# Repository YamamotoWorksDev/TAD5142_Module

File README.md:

# TAD5142 Module

This module board is a headphone output module featuring TI’s stereo audio DAC TAD5142. It supports sample rates up to 192 kHz and can add a headphone output to your microcontroller board or other hardware via an I2S connection.

## How to buy
- Tindie(International)  
- [BASE(Japan)](https://miyworks.base.shop/items/141803009)

## Specifications
- Power: 5V input, onboard 3.3V regulator (AP7361)
- DAC IC: [TAD5142](https://www.ti.com/product/TAD5142)
  - Channels: stereo output
  - Sample Rate: 192kHz(max.)
  - I2S Slave
- Audio Jack: [Green Thonkiconn Stereo 3.5mm Jack Socket](https://www.thonk.co.uk/shop/thonkiconn/)
- Power IC: [AP7361EA-33E-13](https://www.diodes.com/assets/Datasheets/AP7361EA.pdf)

## Application Example
- [JUMBLEQ](https://github.com/yamamo2shun1/JUMBLEQ)

## Size

## Photos

## License
The hardware design files in this repository are licensed under the
**CERN Open Hardware Licence Version 2 - Permissive (CERN-OHL-P-2.0)**.

Unless otherwise stated, the following are treated as hardware design files covered by CERN-OHL-P-2.0:

- KiCad schematic files
- PCB layout files

A copy of the license text is provided in the `LICENSE` file.

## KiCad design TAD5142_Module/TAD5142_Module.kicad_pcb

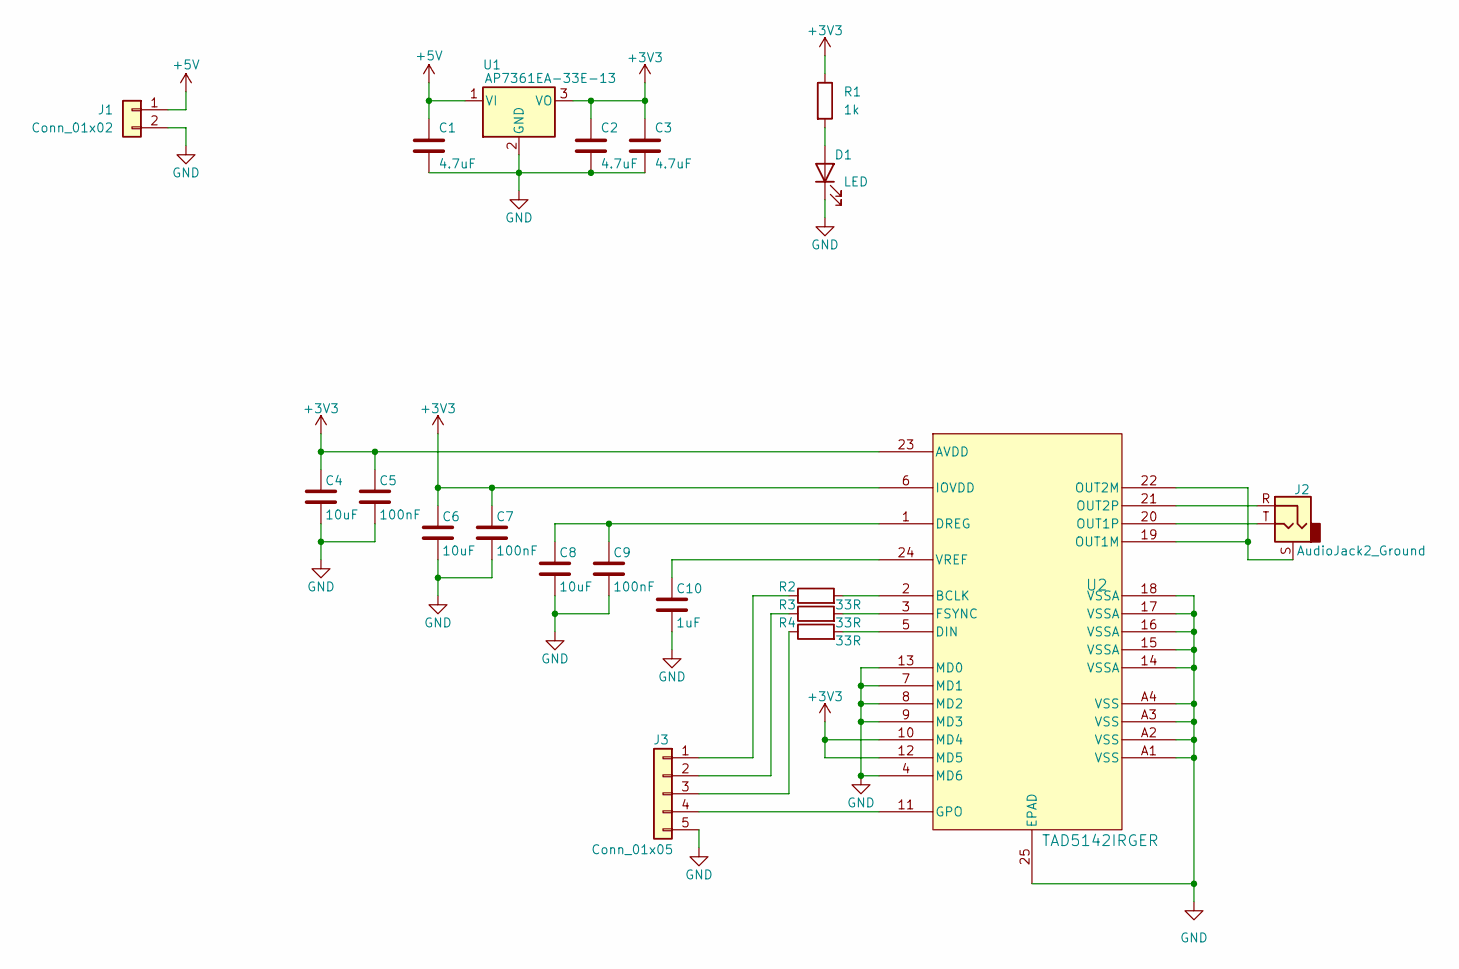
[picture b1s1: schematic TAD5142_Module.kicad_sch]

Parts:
C1, C2, C3: 4.7uF; C_0603_1608Metric
C4, C6, C8: 10uF; C_0402_1005Metric
C5, C7, C9: 100nF; C_0201_0603Metric
C10: 1uF; C_0201_0603Metric
D1: LED; LED_0603_1608Metric
J1: Conn_01x02; JST_PH_B2B-PH-K_1x02_P2.00mm_Vertical
J2: AudioJack2_Ground; Jack_3.5mm_QingPu_WQP-PJ366ST_Vertical
J3: Conn_01x05; PinHeader_1x05_P2.54mm_Vertical
R1: 1k; R_0201_0603Metric
R2, R3, R4: 33R; R_0201_0603Metric
U1: AP7361EA-33E-13; SOT-223-3_TabPin2
U2: TAD5142IRGER; VQFN24_RGE-N_TEX

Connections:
+3V3: C2.1, C3.1, C4.1, C5.1, C6.1, C7.1, R1.1, U1.3 (VO), U2.6 (IOVDD), U2.10 (MD4), U2.12 (MD5), U2.23 (AVDD)
+5V: C1.1, J1.1, U1.1 (VI)
GND: C1.2, C2.2, C3.2, C4.2, C5.2, C6.2, C7.2, C8.2, C9.2, C10.2, D1.1 (K), J1.2, J3.5, U1.2 (GND), U2.4 (MD6), U2.7 (MD1), U2.8 (MD2), U2.9 (MD3), U2.13 (MD0), U2.14 (VSSA), U2.15 (VSSA), U2.16 (VSSA), U2.17 (VSSA), U2.18 (VSSA), U2.25 (EPAD), U2.A1 (VSS), U2.A2 (VSS), U2.A3 (VSS), U2.A4 (VSS)
unnamed: D1.2 (A), R1.2
unnamed: J3.1, R2.1
unnamed: J3.2, R3.1
unnamed: J3.3, R4.1
unnamed: J3.4, U2.11 (GPO)
unnamed: R2.2, U2.2 (BCLK)
unnamed: R4.2, U2.5 (DIN)
unnamed: C8.1, C9.1, U2.1 (DREG)
unnamed: R3.2, U2.3 (FSYNC)
unnamed: J2.S, U2.19 (OUT1M), U2.22 (OUT2M)
unnamed: J2.T, U2.20 (OUT1P)
unnamed: J2.R, U2.21 (OUT2P)
unnamed: C10.1, U2.24 (VREF)

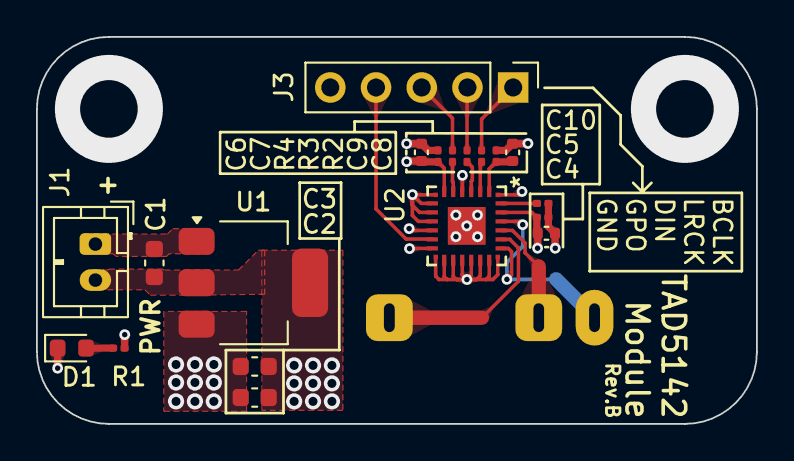
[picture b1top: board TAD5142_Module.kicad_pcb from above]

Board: 4 copper layers, 40.0 x 21.5 mm, 20 parts (1 on the bottom side), 16 nets.

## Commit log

2026-03-27 Add .gitignore
    Exclude CAD STEP files, local module backups, and manufacturing output directories from version control.
2026-03-27 Add KiCAD project files.
2026-03-27 Add CERN Open Hardware Licence v2 Permissive
2026-03-27 Update README with module details and specifications
    Added detailed information about the TAD5142 module, including specifications, purchasing options, and licensing.
2026-03-27 Add TAD5142 module revision A schematic PDF
2026-03-27 Update README.md with image for application size
2026-03-27 Add PCB dimensions.
2026-03-27 Move TAD5142 module files into a subdirectory
    Organize the repository by moving the KiCad project files from the root into a dedicated folder.
2026-04-07 Update TAD5142 module to Revision B
    - Update silkscreen text and board metadata to Revision B.
    - Adjust PCB edge cuts, dimensions, and mounting hole configuration.
    - Correct pad mapping and positioning for the 3.5mm jack (J2).
    - Update footprint info cache with Samtec EdgeRate connectors and remove unused hand-soldering variants.
    - Add teardrops to several component pads and vias for improved reliability.
2026-04-07 Add application example link to README
2026-04-14 Add photos to README
    Added photos to the README for better visualization.
2026-04-15 Update purchase link for BASE(Japan) in README
2026-04-15 Clean up symbol placement
2026-04-15 Renew
